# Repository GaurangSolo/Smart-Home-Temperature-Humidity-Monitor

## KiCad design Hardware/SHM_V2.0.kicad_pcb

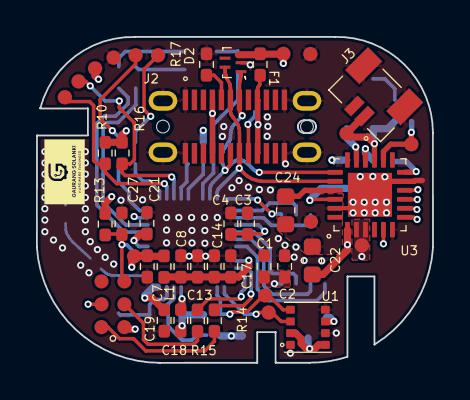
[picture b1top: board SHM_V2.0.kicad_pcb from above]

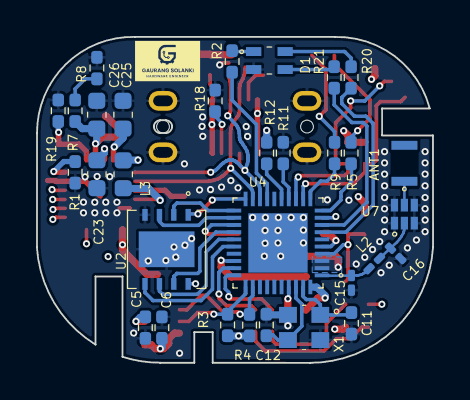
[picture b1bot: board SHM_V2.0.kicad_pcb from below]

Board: 4 copper layers, 22.0 x 18.1 mm, 76 parts (31 on the bottom side), 51 nets.

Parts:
ANT1: ANT2012LL00R2400A; ANTC2012X120N
C1, C3, C5, C7, C14, C19, C21: 0.1uF; R_0402_1005Metric_Pad0.72x0.64mm_HandSolder
C2: locked; R_0402_1005Metric_Pad0.72x0.64mm_HandSolder
C4, C13, C17, C27: 1uF; R_0402_1005Metric_Pad0.72x0.64mm_HandSolder
C6, C8, C18: 10uF; R_0402_1005Metric_Pad0.72x0.64mm_HandSolder
C11, C12: 8pF; R_0402_1005Metric_Pad0.72x0.64mm_HandSolder
C15, C16: 1.2pF; C_0201_0603Metric_Pad0.64x0.40mm_HandSolder
C22, C23, C24: 10uF; C_0603_1608Metric
C25: 2.2nF; C_0603_1608Metric
C26: 1uF; C_0603_1608Metric
D1: QBLP600-RGB; LED_QBLP600-RGB
D2: HSP053-4M5; MICROQFN-5L_STM
F1: 1206L110/16WR; R_0402_1005Metric_Pad0.72x0.64mm_HandSolder
J2: USB4160-03-0230-C_REVA2; GCT_USB4160-03-0230-C_REVA2
J3: SM02B-SURS-TF; CONN_SM02B-SURS-TF_JST
JP1: Jumper_2_Bridged; Jumper
L1: 2.0nH; R_0402_1005Metric_Pad0.72x0.64mm_HandSolder
L2: 2.7nH; C_0201_0603Metric_Pad0.64x0.40mm_HandSolder
L3: 2.2µH; C_0603_1608Metric
R1: 1.5k; R_0402_1005Metric_Pad0.72x0.64mm_HandSolder
R2: 40R; R_0402_1005Metric_Pad0.72x0.64mm_HandSolder
R3, R4, R17, R18: 5.1k; R_0402_1005Metric_Pad0.72x0.64mm_HandSolder
R5, R9, R14, R15: 499R; R_0402_1005Metric_Pad0.72x0.64mm_HandSolder
R7: 47k; R_0402_1005Metric_Pad0.72x0.64mm_HandSolder
R8: 100k; R_0402_1005Metric_Pad0.72x0.64mm_HandSolder
R10, R11, R12, R13, R16, R19: 10k; R_0402_1005Metric_Pad0.72x0.64mm_HandSolder
R20: 60R; R_0402_1005Metric_Pad0.72x0.64mm_HandSolder
R21: 220R; R_0402_1005Metric_Pad0.72x0.64mm_HandSolder
TC1: DNP; TC2030-IDC-NL2
TP1, TP2, TP3, TP4, TP5, TP6, TP7, TP8, TP9, TP10, TP11, TP12, TP13, TP14, TP15: DNP; TestPoint_Pad_D1.0mm
U1: BME280; PSON65P250X250X100-8N
U2: W25Q64JVXGIQ TR; DFN_XGIQ TR_WIN-L
U3: NPM1100-QDAA-R; QFN50P400X400X100-25N
U4: ESP32-C6; QFN40P500X500X90-41N
U7: DEA162500LT-1217A1; DEA-6_1P6X0P8
X1: R2520-40.000-8-F-1010-TR-NS3; R2520-40.000-10-F-1010-EXT-TR_RAL

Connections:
+3V0: C5.1, C6.1, C8.1, C13.1, C14.1, C17.1, C18.1, C19.1, C21.1, C22.1, L1.2, L3.2, R3.2, R4.2, R10.2, R12.2, R13.2, R16.2, TC1.1, TP12.1, U1.2 (CSB), U1.6 (VDDIO), U1.8 (VDD), U3.1 (VOUTB), U4.5 (VDDPST1), U4.28 (VDDPST2), U4.37 (VDDA1), U4.40 (VDDA2)
+BATT: C26.1, J3.1, R7.1, TP7.1, U3.15 (VBAT)
BAT_MON_ADC: R7.2, R8.1
ESP_EN: C27.1, R13.1, TC1.5, U4.4 (CHIP_PU)
ESP_I09: TC1.4, U4.9 (GPIO3)
ESP_RXD: R15.1, TC1.3
ESP_R_STRAP8: R11.2, U4.14 (GPIO8)
ESP_R_STRAP9: R12.1, U4.15 (GPIO9)
ESP_TXD: R14.1, TC1.2
GND: C1.2, C2.2, C3.2, C4.2, C5.2, C6.2, C7.2, C8.2, C11.2, C12.2, C13.2, C14.2, C15.2, C16.2, C17.2, C18.2, C19.2, C21.2, C23.2, C25.2, C26.2, C27.2, D1.3, D2.2, J2.A1 (GND_A), J2.A12 (GND_A__1), J2.B1 (GND_B), J2.B12 (GND_B__1), J2.S1 (SHIELD), J2.S2 (SHIELD__1), J2.S3 (SHIELD__2), J2.S4 (SHIELD__3), J3.2, J3.3, J3.4, R1.2, R8.2, R11.1, R17.1, R18.1, R19.1, TP2.1, TP13.1, U1.1 (GND), U1.5 (SDO), U1.7 (GND__1), U2.4 (GND), U2.9, U3.6 (SHPACT), U3.11 (SHPHLD), U3.25 (GND), U4.41 (GND), U7.1 (GND), U7.3 (GND), U7.4 (GND), U7.6 (GND), X1.2, X1.4
I2C1_SCL: R16.1, TP15.1, U4.13 (GPIO7/MTDO)
I2C1_SDA: R10.1, TP14.1, U4.12 (GPIO6/MTCK)
I2C2_SCL: R4.1, TP9.1, U1.4 (SCK), U4.32 (SDIO_CLK/GPIO19)
I2C2_SDA: R3.1, TP8.1, U1.3 (SDI), U4.31 (SDIO_CMD/GPIO18)
LED_BLUE: R2.2, U4.17 (GPIO11)
LED_GREEN: R20.2, U4.7 (GPIO1/XTAL_32K_N)
LED_RED: R21.2, U4.8 (GPIO2)
unnamed: ANT1.1 (FEED), U7.5 (OUT)
unnamed: D1.1, R2.1
unnamed: D1.2, R20.1
unnamed: D1.4, R21.1
unnamed: J2.A5 (CC1), R17.2
unnamed: J2.B5 (CC2), R18.2
unnamed: F1.2, J2.A4 (VBUS_A), J2.A9 (VBUS_A__1), J2.B4 (VBUS_B), J2.B9 (VBUS_B__1)
unnamed: C24.1, U3.21 (DEC)
unnamed: R1.1, U3.12 (ICHG)
unnamed: R19.2, TP4.1, U3.14 (NTC)
unnamed: L3.1, U3.22 (SW)
unnamed: C15.1, L2.1, U4.1 (ANT)
unnamed: R5.1, U4.10 (GPIO4/MTMS)
unnamed: R9.1, U4.11 (GPIO5/MTDI)
unnamed: R15.2, U4.30 (U0RXD/GPIO17)
unnamed: R14.2, U4.29 (U0TXD/GPIO16)
unnamed: C12.1, U4.38 (XTAL_N), X1.3
unnamed: C11.1, U4.39 (XTAL_P), X1.1
unnamed: C16.1, L2.2, U7.2 (IN)
PVSS: C22.2, C24.2, TP10.1, U3.23 (PVSS)
SPICLK: U2.6 (CLK), U4.25 (SPICLK/GPIO29)
SPICS: U2.1 (/CS), U4.20 (SPICS0/GPIO24)
SPID: U2.5 (DI_(IO0)), U4.26 (SPID/GPIO30)
SPIHD: U2.7 (/HOLD_or_/RESET_(IO3)), U4.24 (SPIHD/GPIO28)
SPIQ: U2.2 (DO_(IO1)), U4.21 (SPIQ/GPIO25)
SPIWP: U2.3, U4.22 (SPIWP/GPIO26)
UART1_RX: R5.2, TP1.1
UART1_TX: R9.2, TP3.1
USB_D+: D2.5, J2.A6 (DP1), J2.B6 (DP2), U3.20 (D+), U4.19 (USB_D+/GPIO13)
USB_D-: D2.1, J2.A7 (DN1), J2.B7 (DN2), U3.19 (D-), U4.18 (USB_D-/GPIO12)
VBUS: C25.1, D2.3, F1.1, TP6.1, U3.17 (VBUS)
VCC: C7.1, L1.1, TP11.1, U4.2 (VDDA3P3), U4.3 (VDDA3P3__1)
VCOM: C1.1, C2.1, C3.1, C4.1, U2.8 (VCC), U4.23 (VDD_SPI)
VSYS: C23.1, TP5.1, U3.2 (VOUTBSET1), U3.3 (VOUTBSET2), U3.9 (VTERMSET), U3.16 (VSYS)

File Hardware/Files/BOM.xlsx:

Reference | Value | Purchase Link | Manufacturer | Part Number | Price | Qty
ANT1 | ANT2012LL00R2400A | ANT2012LL00R2400A Pulse Electronics | RF and Wireless | DigiKey | Pulse Electronics | ANT2012LL00R2400A | 0.39 | 1.0
C1, C3, C5, C7, C14, C19, C21 | 0.1uF | CL05B104KP5NNNC Samsung Electro-Mechanics | Capacitors | DigiKey | Samsung Electro-Mechanics | CL05B104KP5NNNC | 0.0053 | 7.0
C2, C6, C8, C18 | 10uF | GRM155R61A106ME11D Murata Electronics | Capacitors | DigiKey | Murata Electronics | GRM155R61A106ME11D | 0.0365 | 4.0
C4, C13, C17, C27 | 1uF | CL05A105KA5NQNC Samsung Electro-Mechanics | Capacitors | DigiKey | Samsung Electro-Mechanics | CL05A105KA5NQNC | 0.0459 | 4.0
C11, C12 | 8pF | CL05C080DB51PNC Samsung Electro-Mechanics | Capacitors | DigiKey | Samsung Electro-Mechanics | CL05C080DB51PNC | 0.0249 | 2.0
C15, C16 | 1.2pF | GRM0335C1E1R2BA01D Murata Electronics | Capacitors | DigiKey | Murata Electronics | GRM0335C1E1R2BA01D | 0.0144 | 2.0
C22-C24 | 10uF | CL10A106KQ8NNNC Samsung Electro-Mechanics | Capacitors | DigiKey | Samsung Electro-Mechanics | CL10A106KQ8NNNC | 0.0259 | 3.0
C25 | 2.2nF/2200pF | C0603C222K5RACTU KEMET | Capacitors | DigiKey | KEMET | C0603C222K5RACTU | 0.0247 | 1.0
C26 | 1uF | CL10B105KP8NNNC Samsung Electro-Mechanics | Capacitors | DigiKey | Samsung Electro-Mechanics | CL10B105KP8NNNC | 0.007 | 1.0
D1 | QBLP600-RGB | QBLP600-RGB QT Brightek (QTB) | Capacitors | DigiKey | QT Brightek (QTB) | QBLP600-RGB | 0.389 | 1.0
D2 | HSP053-4M5 | HSP053-4M5 STMicroelectronics | Capacitors | DigiKey | STMicroelectronics | HSP053-4M5 | 0.1463 | 1.0
F1 | 1206L110/16WR | 1206L110/16WR Littelfuse Inc. | Capacitors | DigiKey | Littelfuse Inc. | 1206L110/16WR | 0.934 | 1.0
J2 | USB4160-03-0230-C | USB4160-03-0230-C GCT | Capacitors | DigiKey | GCT | USB4160-03-0230-C | 1.2583 | 1.0
J3 | SM02B-SURS-TF | SM02B-SURS-TF JST Sales America Inc. | Capacitors | DigiKey | JST Sales America Inc. | SM02B-SURS-TF | 0.5836 | 1.0
JP1 | Jumper_2_Bridged |  |  | DNP |  | 1.0
L1 | 2.0nH | LQG15HN2N0C02D Murata Electronics | Capacitors | DigiKey | Murata Electronics | LQG15HN2N0C02D | 0.0526 | 1.0
L2 | 2.7nH | LQP03TN2N7B02D Murata Electronics | Capacitors | DigiKey | Murata Electronics | LQP03TN2N7B02D | 0.0353 | 1.0
L3 | 2.2ÂµH | CS160808-2R2K Bourns Inc. | Capacitors | DigiKey | Bourns Inc. | CS160808-2R2K | 0.0906 | 1.0
R1 | 1.5k | ERJ-2GEJ152X Panasonic Electronic Components | Capacitors | DigiKey | Panasonic Electronic Components | ERJ-2GEJ152X | 0.0196 | 1.0
R2 | 40.2R | RMCF0402FT40R2 Stackpole Electronics Inc | Capacitors | DigiKey | Stackpole Electronics Inc | RMCF0402FT40R2 | 0.0135 | 1.0
R3, R4, R17, R18 | 5.1k | RC0402FR-075K1L YAGEO | Capacitors | DigiKey | YAGEO | RC0402FR-075K1L | 0.0096 | 4.0
R5, R9, R14, R15 | 499R | RC0402FR-07499RL YAGEO | Capacitors | DigiKey | YAGEO | RC0402FR-07499RL | 0.0096 | 4.0
R7 | 47k | RC0402FR-0747KL YAGEO | Capacitors | DigiKey | YAGEO | RC0402FR-0747KL | 0.0111 | 1.0
R8 | 100k | RC0402JR-07100KL YAGEO | Capacitors | DigiKey | YAGEO | RC0402JR-07100KL | 0.008 | 1.0
R10-R13, R16, R19 | 10k | RC0402JR-0710KL YAGEO | Capacitors | DigiKey | YAGEO | RC0402JR-0710KL | 0.0096 | 6.0
R20 | 60.4R | TFA0402R6042F-T10 Thin Film Technology Corp. | Capacitors | DigiKey | Thin Film Technology Corp. | TFA0402R6042F-T10 | 0.0134 | 1.0
R21 | 220R | RC0402FR-07220RL YAGEO | Capacitors | DigiKey | YAGEO | RC0402FR-07220RL | 0.0096 | 1.0
TC1 | DNP | TC2030-IDC Tag-Connect LLC | Capacitors | DigiKey | Tag-Connect LLC | TC2030-IDC |  | 1.0
TP1-TP15 | DNP |  |  | DNP |  | 15.0
U1 | BME280 | BME280 Bosch Sensortec | Capacitors | DigiKey | Bosch Sensortec | BME280 | 4.7649 | 1.0
U2 | W25Q64JVXGIQ TR | W25Q64JVXGIQ TR Winbond Electronics | Capacitors | DigiKey | Winbond Electronics | W25Q64JVXGIQ TR | 1.3578 | 1.0
U3 | NPM1100-QDAA-R | NPM1100-QDAA-R Nordic Semiconductor | Capacitors | DigiKey | Nordic Semiconductor | NPM1100-QDAA-R | 1.4698 | 1.0
U4 | ESP32-C6 | ESP32-C6 Espressif Systems | Capacitors | DigiKey | Espressif Systems | ESP32-C6 | 3.18 | 1.0
U7 | DEA162500LT-1217A1 | DEA162500LT-1217A1 TDK Corporation | Capacitors | DigiKey | TDK Corporation | DEA162500LT-1217A1 | 0.2966 | 1.0
X1 | R2520-40.000-8-F-1010-TR-NS3 | R2520-40.000-8-F-1010-TR-NS3 Raltron Electronics | Capacitors | DigiKey | Raltron Electronics | R2520-40.000-8-F-1010-TR-NS3 | 0.2363 | 1.0

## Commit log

2025-04-10 Added all files
2025-04-12 fixed main.c
2025-04-12 Added interrupt
2025-05-13 Added hardware files and organized project files.
    - Added hardware design files including schematics, PCB layout, and BOM for the smart home monitoring system.
    - Organized project structure into /hardware and /firmware directories for clarity.
    - Included README files in respective folders to describe build and usage instructions.
    This commit sets up the foundation for further development and documentation.
2025-05-13 Major firmware change due to component change
    -Removed STM32 from hardware
2025-05-13 Added README
2025-05-13 Created architecture
